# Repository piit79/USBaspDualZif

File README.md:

# USBaspDualZif

USB in-circuit programmer for Atmel AVR controllers based on USBasp by Thomas Fischl (https://www.fischl.de/usbasp/).

It adds the following extra features:

  * Dual ZIF sockets for ATMega32A-PU and ATMega328p-PU
  * One Cherry MX-compatible switch that acts as the Enter key
  * USB-C socket

Uses mostly SMD components for street cred.

Modified firmware: https://github.com/piit79/USBasp/tree/USBaspDualZif

Released under the [GNU General Public License v2.0](https://raw.githubusercontent.com/piit79/USBaspDualZif/main/LICENSE) (as it's based on USBasp)

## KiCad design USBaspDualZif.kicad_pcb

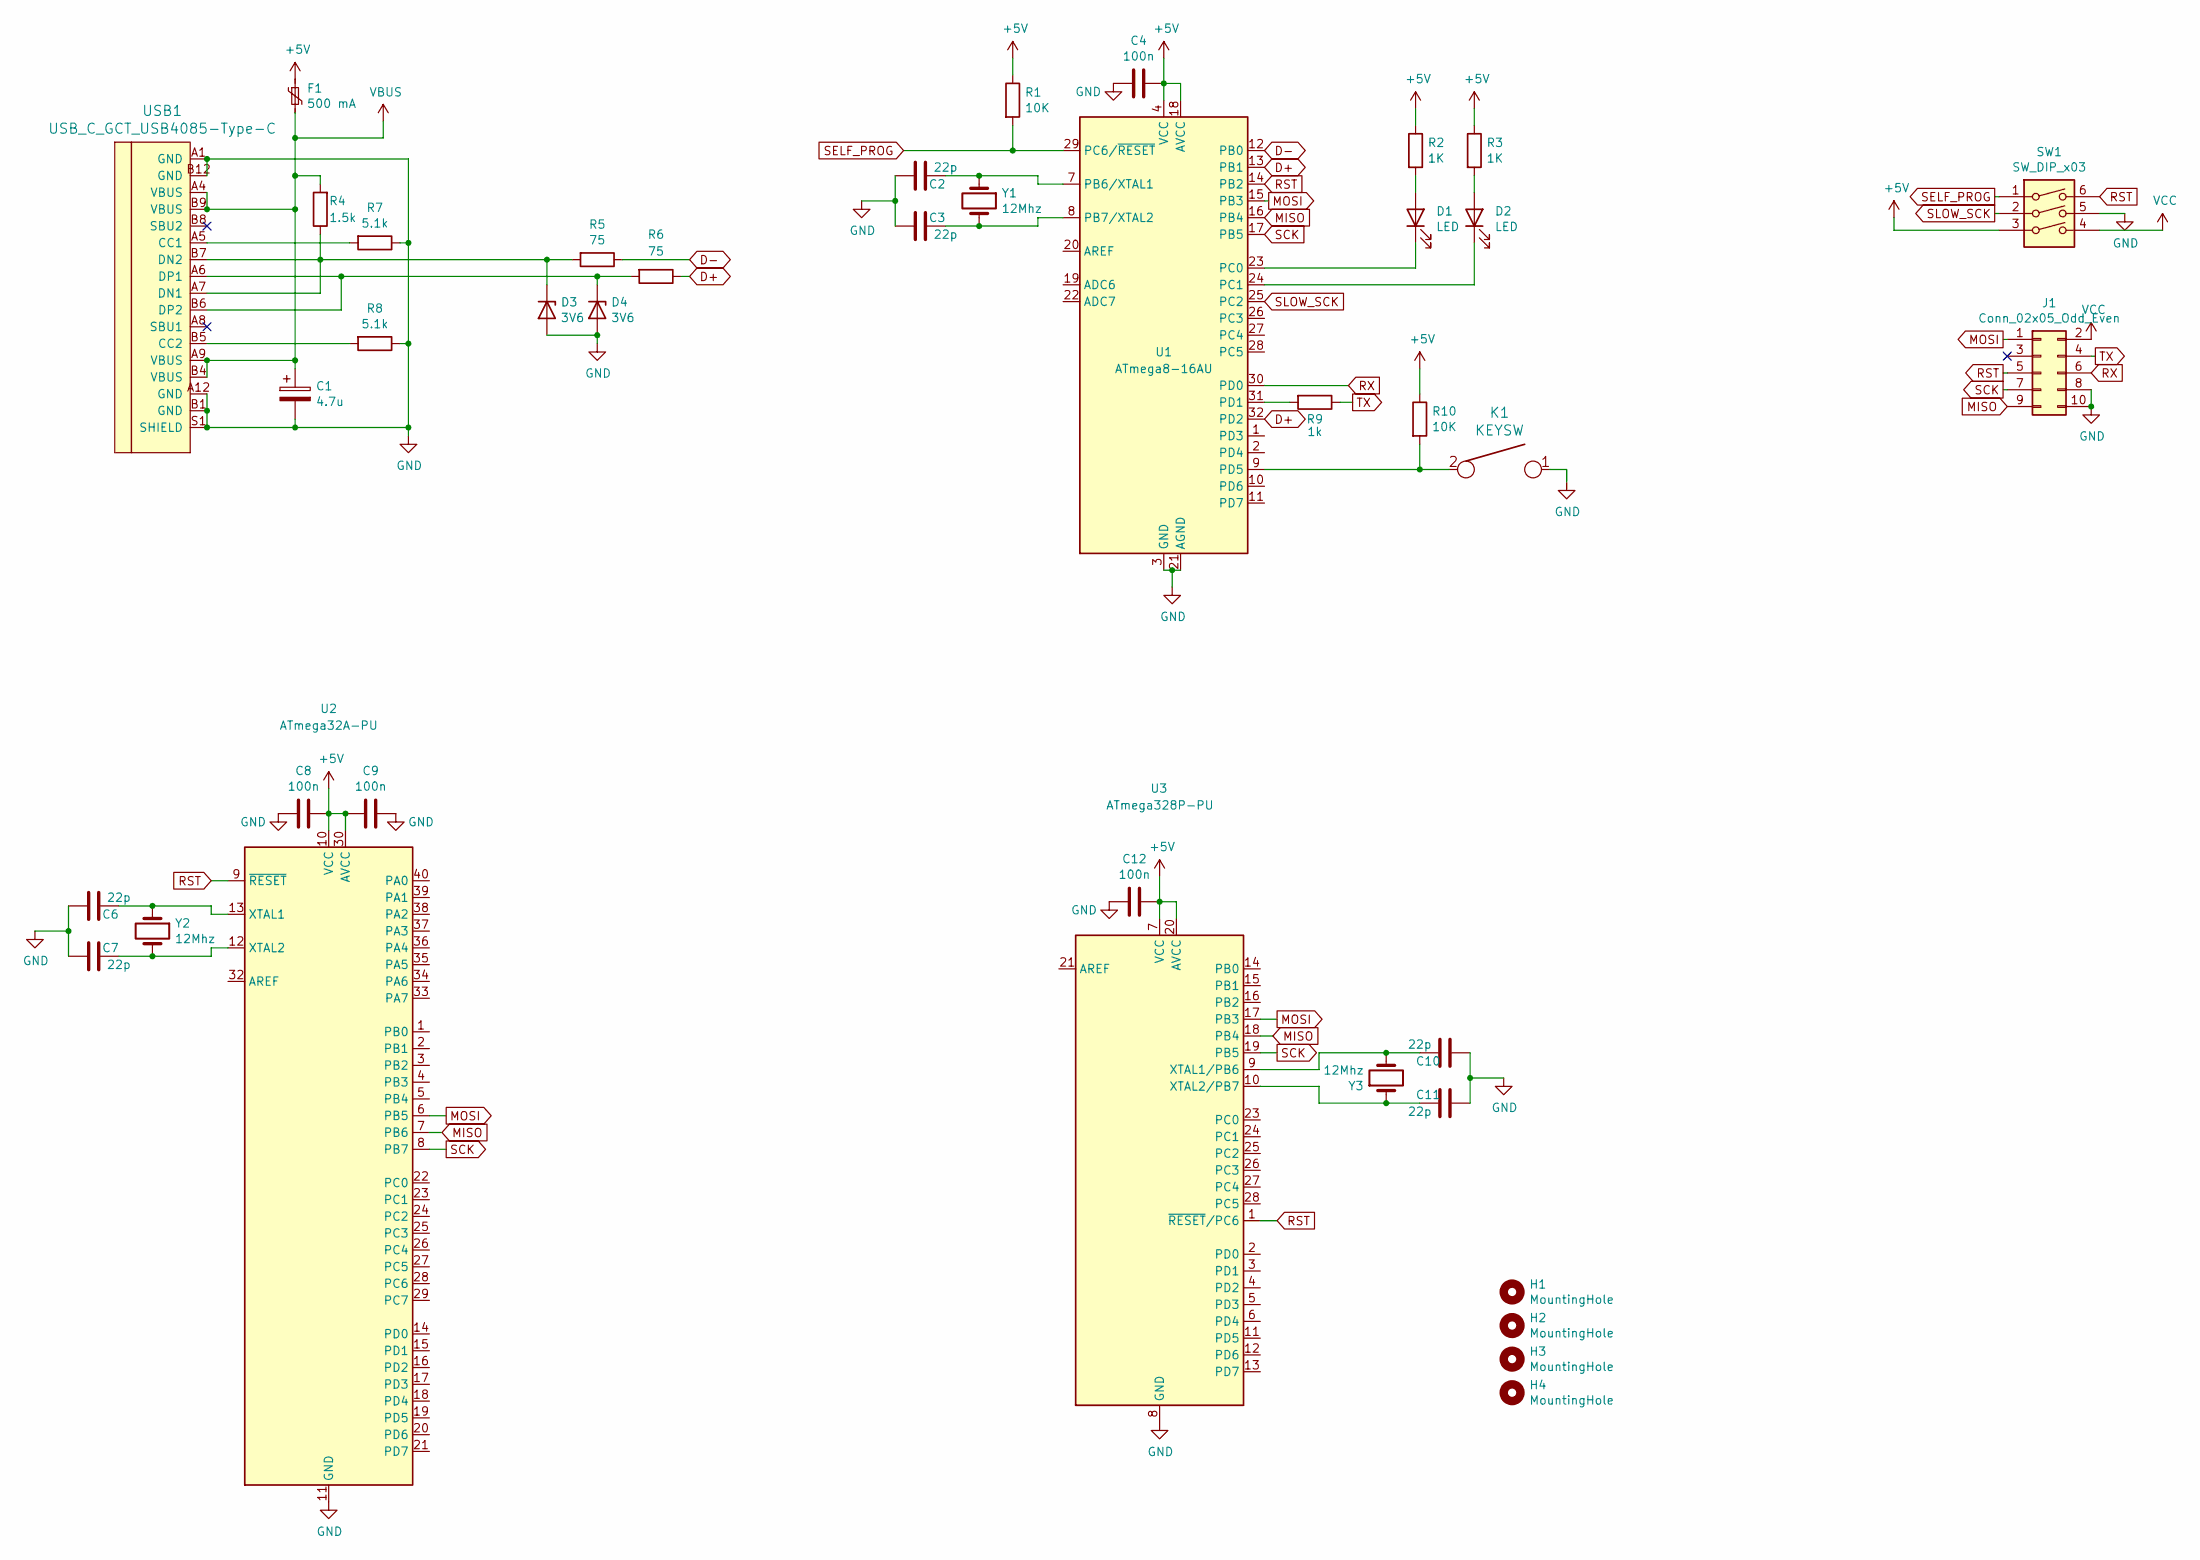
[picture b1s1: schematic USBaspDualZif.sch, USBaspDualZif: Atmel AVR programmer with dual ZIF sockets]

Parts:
C1: 4.7u; C_0805_2012Metric
C2, C3, C6, C7, C10, C11: 22p; C_0805_2012Metric
C4, C8, C9, C12: 100n; C_0805_2012Metric
D1, D2: LED; LED_0805_2012Metric
D3, D4: 3V6; D_SOD-123
F1: 500 mA; Fuse_1812_4532Metric
H1, H2, H3, H4: MountingHole; MountingHole_2.2mm_M2_Pad
J1: Conn_02x05_Odd_Even; IDC-Header_2x05_P2.54mm_Vertical
K1: KEYSW; SW_Cherry_MX1A_1.00u_PCB-NOSCREEN
R1, R10: 10K; R_0805_2012Metric
R2, R3: 1K; R_0805_2012Metric
R4: 1.5k; R_0805_2012Metric
R5, R6: 75; R_0805_2012Metric
R7, R8: 5.1k; R_0805_2012Metric
R9: 1k; R_0805_2012Metric
SW1: SW_DIP_x03; SW_DIP_SPSTx03_Slide_9.78x9.8mm_W7.62mm_P2.54mm
U1: ATmega8-16AU; TQFP-32_7x7mm_P0.8mm
U2: ATmega32A-PU; 40tex600
U3: ATmega328P-PU; 28tex600
USB1: USB_C_GCT_USB4085-Type-C; USB_C_GCT_USB4085-offset-pads
Y1, Y2, Y3: 12Mhz; Crystal_HC49-4H_Vertical

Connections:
+5V: C4.1, C8.1, C9.2, C12.1, F1.1, R1.1, R2.1, R3.1, R10.1, SW1.3, U1.4 (VCC), U1.6 (VCC), U1.18 (AVCC), U2.10 (VCC), U2.30 (AVCC), U3.7 (VCC), U3.20 (AVCC)
D+: R6.1, U1.13 (PB1), U1.32 (PD2)
D-: R5.1, U1.12 (PB0)
GND: C1.2, C2.2, C3.2, C4.2, C6.2, C7.2, C8.2, C9.1, C10.2, C11.2, C12.2, D3.2 (A), D4.2 (A), J1.8, J1.10, K1.1, R7.1, R8.1, SW1.5, U1.3 (GND), U1.5 (GND), U1.21 (AGND), U2.11 (GND), U2.31 (GND), U3.8 (GND), U3.22 (GND), USB1.A1 (GND), USB1.A12 (GND), USB1.B1 (GND), USB1.B12 (GND), USB1.S1 (SHIELD)
MISO: J1.9, U1.16 (PB4), U2.7 (PB6), U3.18 (PB4)
MOSI: J1.1, U1.15 (PB3), U2.6 (PB5), U3.17 (PB3)
unnamed: C2.1, U1.7 (PB6/XTAL1), Y1.1
unnamed: C3.1, U1.8 (PB7/XTAL2), Y1.2
unnamed: C6.1, U2.13 (XTAL1), Y2.1
unnamed: C7.1, U2.12 (XTAL2), Y2.2
unnamed: C10.1, U3.9 (XTAL1/PB6), Y3.2
unnamed: C11.1, U3.10 (XTAL2/PB7), Y3.1
unnamed: D1.1 (K), U1.23 (PC0)
unnamed: D1.2 (A), R2.2
unnamed: D2.1 (K), U1.24 (PC1)
unnamed: D2.2 (A), R3.2
unnamed: D3.1 (K), R4.1, R5.2, USB1.A7 (DN1), USB1.B7 (DN2)
unnamed: D4.1 (K), R6.2, USB1.A6 (DP1), USB1.B6 (DP2)
unnamed: K1.2, R10.2, U1.9 (PD5)
unnamed: R7.2, USB1.A5 (CC1)
unnamed: R8.2, USB1.B5 (CC2)
unnamed: R9.2, U1.31 (PD1)
RST: J1.5, SW1.6, U1.14 (PB2), U2.9 (~RESET), U3.1 (~RESET~/PC6)
RX: J1.6, U1.30 (PD0)
SCK: J1.7, U1.17 (PB5), U2.8 (PB7), U3.19 (PB5)
SELF_PROG: R1.2, SW1.1, U1.29 (PC6/~RESET)
SLOW_SCK: SW1.2, U1.25 (PC2)
TX: J1.4, R9.1
VBUS: C1.1, F1.2, R4.2, USB1.A4 (VBUS), USB1.A9 (VBUS), USB1.B4 (VBUS), USB1.B9 (VBUS)
VCC: J1.2, SW1.4

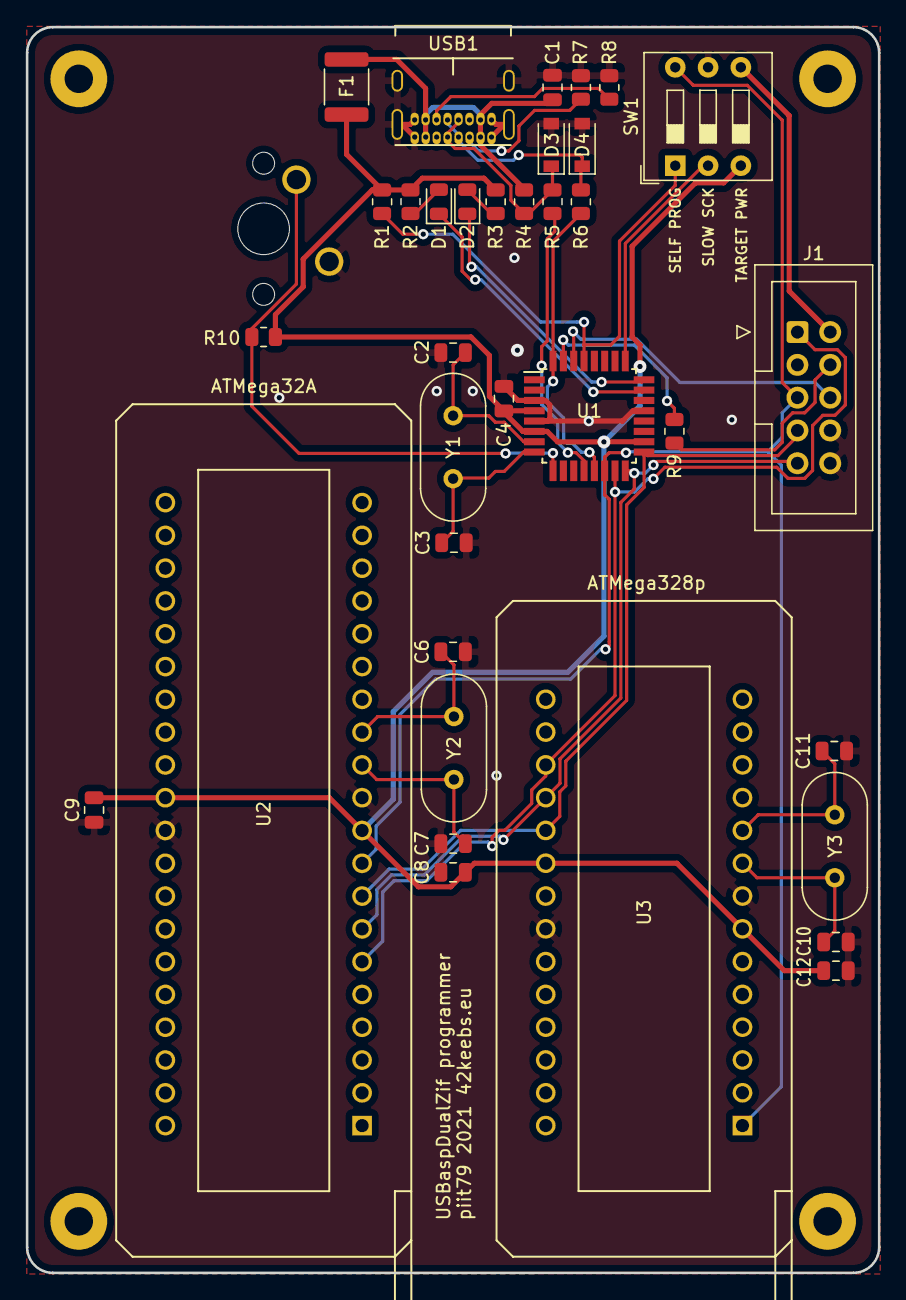
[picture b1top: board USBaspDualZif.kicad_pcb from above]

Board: 2 copper layers, 66.0 x 96.5 mm, 40 parts (0 on the bottom side), 30 nets.

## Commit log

2021-10-12 Add KiCad files
2021-10-12 Add Gerber files
2021-10-12 Update README with license notice and a picture

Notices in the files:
USBaspDualZif.kicad_pcb:
GNU General Public License version 2
